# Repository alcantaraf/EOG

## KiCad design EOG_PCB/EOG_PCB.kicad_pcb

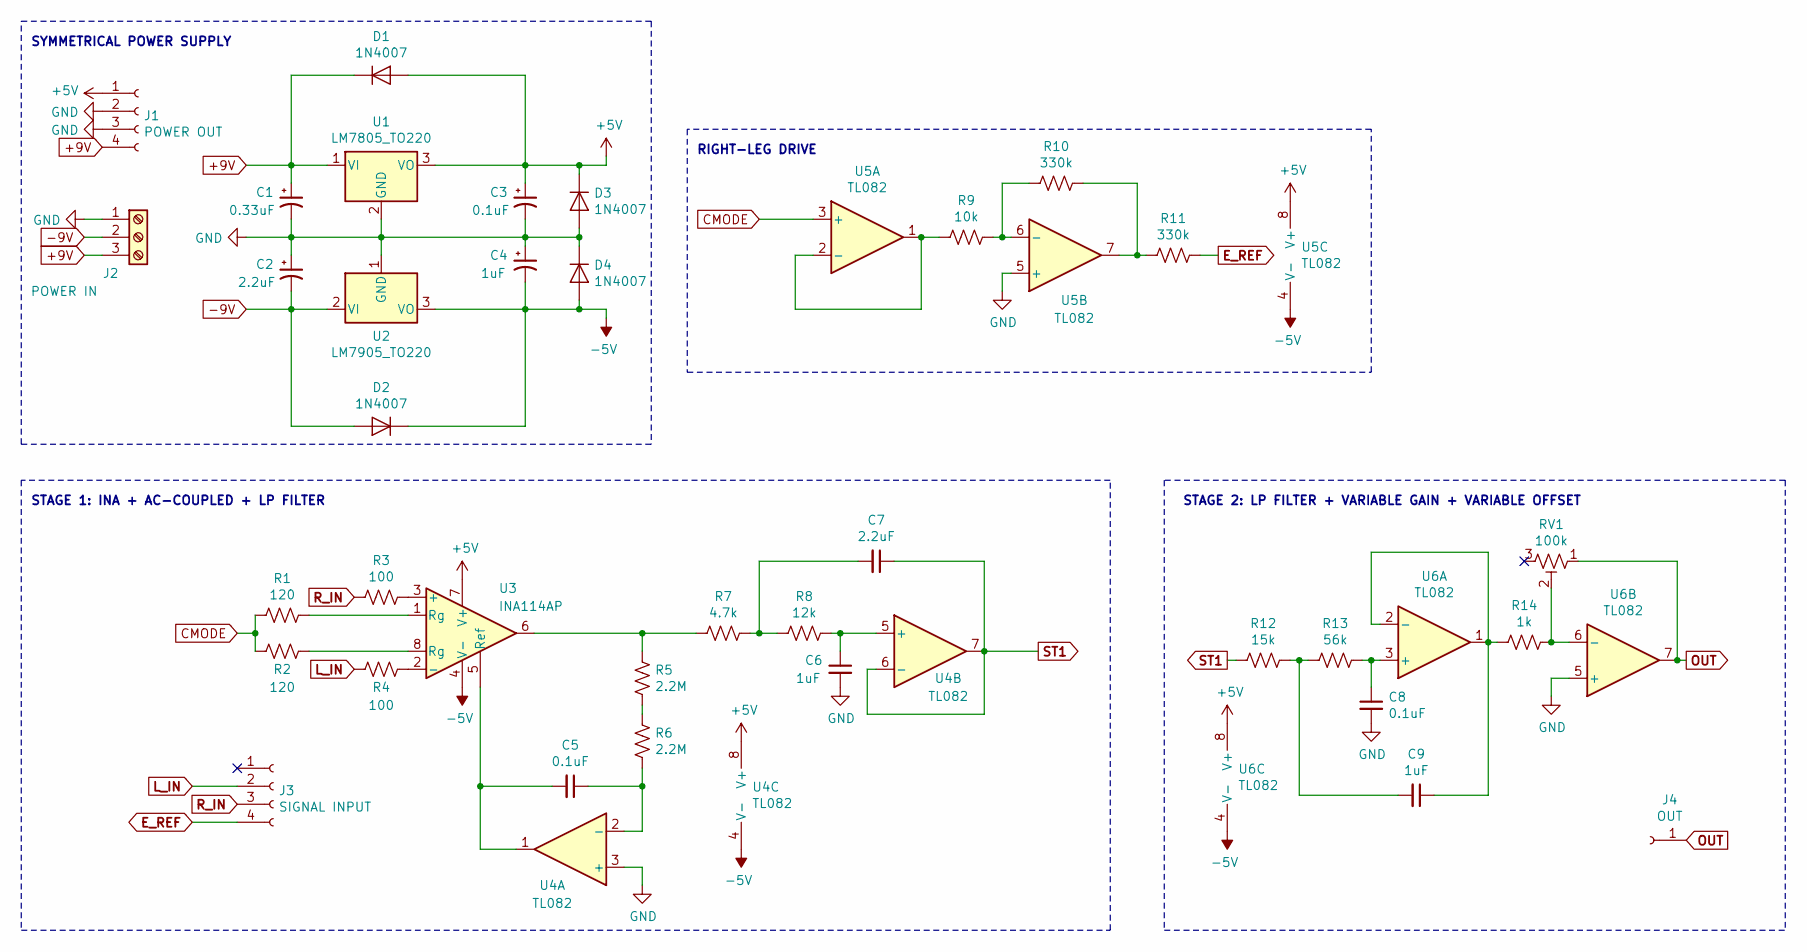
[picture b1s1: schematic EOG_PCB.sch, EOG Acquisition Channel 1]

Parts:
C1: 0.33uF; CP_Radial_Tantal_D4.5mm_P2.50mm
C2: 2.2uF; CP_Radial_D6.3mm_P2.50mm
C3, C5, C8: 0.1uF; C_Rect_L7.2mm_W2.5mm_P5.00mm_FKS2_FKP2_MKS2_MKP2
C4: 1uF; CP_Radial_D6.3mm_P2.50mm
C6, C9: 1uF; C_Rect_L24.0mm_W7.0mm_P22.50mm_MKT
C7: 2.2uF; C_Rect_L24.0mm_W7.0mm_P22.50mm_MKT
D1, D2, D3, D4: 1N4007; D_DO-41_SOD81_P10.16mm_Horizontal
J1: POWER OUT; PinSocket_1x04_P2.54mm_Vertical
J2: POWER IN; TerminalBlock_Philmore_TB133_1x03_P5.00mm_Horizontal
J3: SIGNAL INPUT; PinSocket_1x04_P2.54mm_Vertical
J4: OUT; PinHeader_1x01_P2.54mm_Vertical
R1, R2: 120; R_Axial_DIN0204_L3.6mm_D1.6mm_P5.08mm_Horizontal
R3, R4: 100; R_Axial_DIN0204_L3.6mm_D1.6mm_P5.08mm_Horizontal
R5, R6: 2.2M; R_Axial_DIN0204_L3.6mm_D1.6mm_P5.08mm_Horizontal
R7: 4.7k; R_Axial_DIN0204_L3.6mm_D1.6mm_P5.08mm_Horizontal
R8: 12k; R_Axial_DIN0204_L3.6mm_D1.6mm_P5.08mm_Horizontal
R9: 10k; R_Axial_DIN0204_L3.6mm_D1.6mm_P5.08mm_Horizontal
R10, R11: 330k; R_Axial_DIN0204_L3.6mm_D1.6mm_P5.08mm_Horizontal
R12: 15k; R_Axial_DIN0204_L3.6mm_D1.6mm_P5.08mm_Horizontal
R13: 56k; R_Axial_DIN0204_L3.6mm_D1.6mm_P5.08mm_Horizontal
R14: 1k; R_Axial_DIN0204_L3.6mm_D1.6mm_P5.08mm_Horizontal
RV1: 100k; Potentiometer_Bourns_3386F_Vertical
U1: LM7805_TO220; TO-220-3_Vertical
U2: LM7905_TO220; TO-220-3_Vertical
U3: INA114AP; DIP-8_W7.62mm_Socket_LongPads
U4, U5, U6: TL082; DIP-8_W7.62mm_Socket_LongPads

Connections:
+5V: C3.1, D1.2 (A), D3.1 (K), J1.1, U1.3 (VO), U3.7 (V+), U4.8 (V+), U5.8 (V+), U6.8 (V+)
+9V: C1.1, D1.1 (K), J1.4, J2.3, U1.1 (VI)
-5V: C4.2, D2.1 (K), D4.2 (A), U2.3 (VO), U3.4 (V-), U4.4 (V-), U5.4 (V-), U6.4 (V-)
-9V: C2.2, D2.2 (A), J2.2, U2.2 (VI)
CMODE: R1.2, R2.2, U5.3 (+)
E_REF: J3.4, R11.2
GND: C1.2, C2.1, C3.2, C4.1, C6.2, C8.2, D3.2 (A), D4.1 (K), J1.2, J1.3, J2.1, U1.2 (GND), U2.1 (GND), U4.3 (+), U5.5 (+), U6.5 (+)
L_IN: J3.2, R4.2
unnamed: C5.1, R6.1, U4.2 (-)
unnamed: C5.2, U3.5 (Ref), U4.1
unnamed: C6.1, R8.1, U4.5 (+)
unnamed: C7.2, R7.1, R8.2
unnamed: C8.1, R13.1, U6.3 (+)
unnamed: C9.1, R14.2, U6.1, U6.2 (-)
unnamed: C9.2, R12.1, R13.2
unnamed: R1.1, U3.1 (Rg)
unnamed: R2.1, U3.8 (Rg)
unnamed: R3.1, U3.3 (+)
unnamed: R4.1, U3.2 (-)
unnamed: R5.1, R6.2
unnamed: R5.2, R7.2, U3.6
unnamed: R9.2, U5.1, U5.2 (-)
unnamed: R10.1, R11.1, U5.7
unnamed: R9.1, R10.2, U5.6 (-)
unnamed: R14.1, RV1.2, U6.6 (-)
OUT: J4.1, RV1.1, U6.7
R_IN: J3.3, R3.2
ST1: C7.1, R12.2, U4.6 (-), U4.7

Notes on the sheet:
SYMMETRICAL POWER SUPPLY
RIGHT-LEG DRIVE
STAGE 1: INA + AC-COUPLED + LP FILTER
STAGE 2: LP FILTER + VARIABLE GAIN + VARIABLE OFFSET

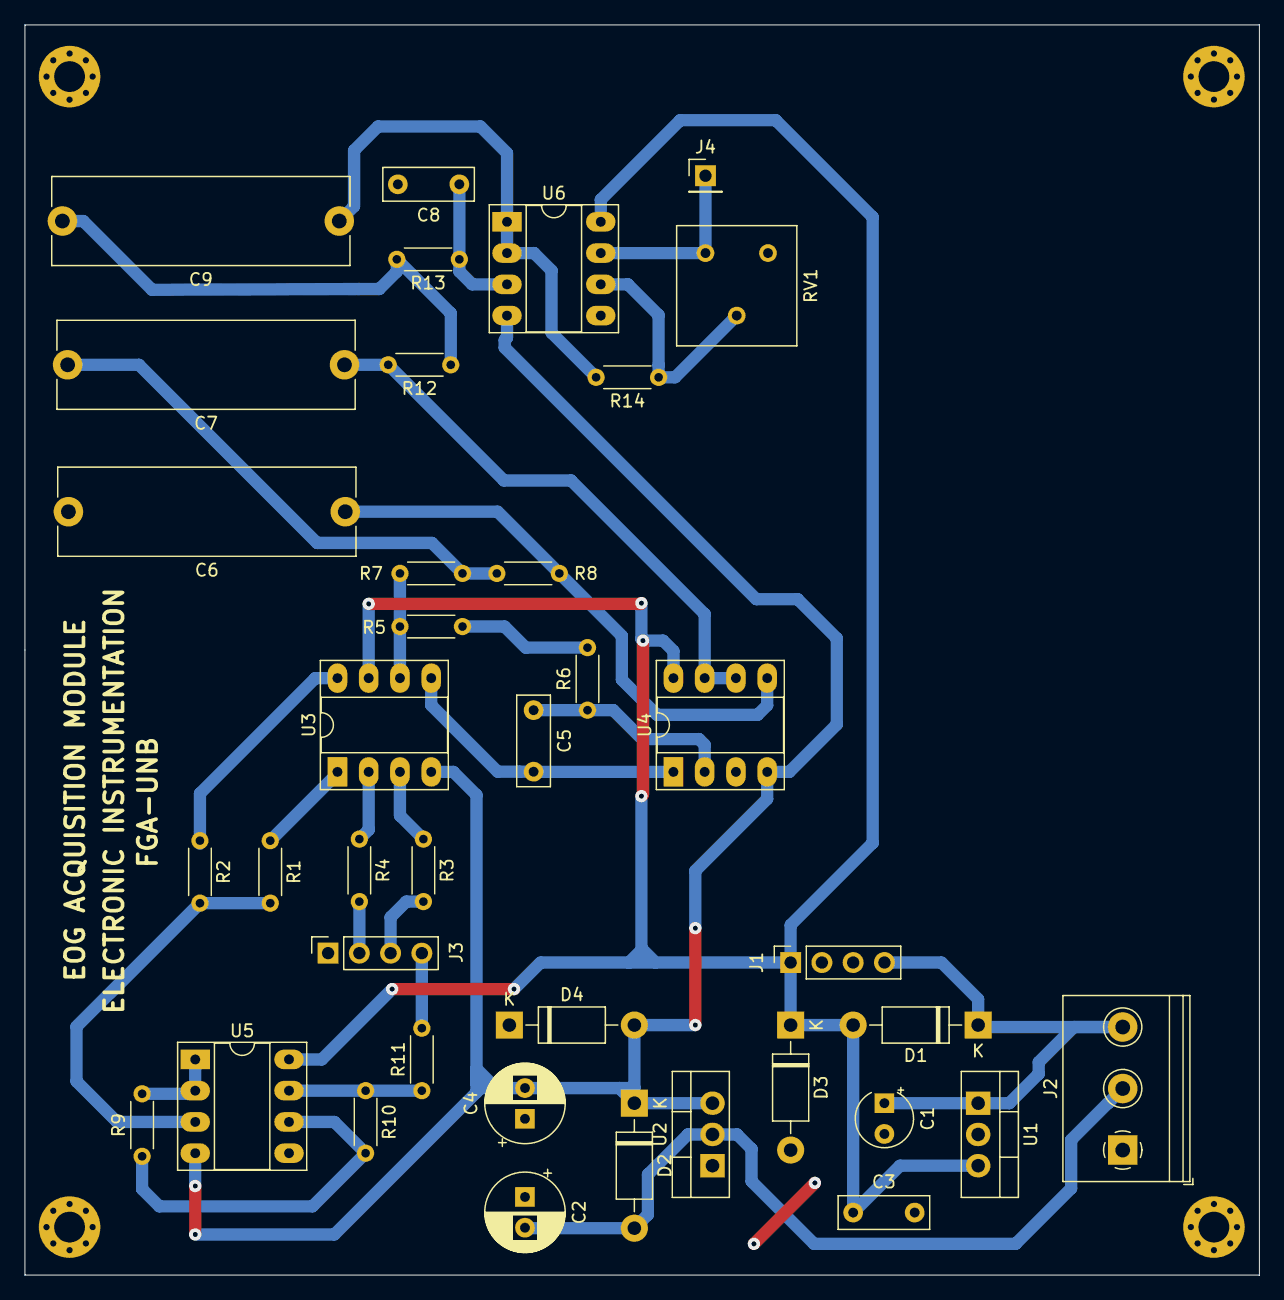
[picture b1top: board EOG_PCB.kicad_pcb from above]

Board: 2 copper layers, 100.3 x 101.6 mm, 38 parts (0 on the bottom side), 28 nets.

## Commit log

2019-12-01 EOG Kicad Schematics V1
2019-12-03 Added Record Signals for some EOG Patterns
2019-12-03 Added PCB Layout & Minor Improvements in sch
2019-12-03 Layout Improvements & Added B-CU, Label pdf files
2019-12-03 Mirrored Label Layer
2019-12-03 Updated EOG Recordings
